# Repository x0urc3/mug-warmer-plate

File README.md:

# [Work-In-Progress] Mug Warmer Plate
A Mug Warmer PCB plate

## To Do
### Version 0.1-test
Create a PCB to test and evaluate hardware and firmware design
- ~~Circuit design~~
- ~~PCB design~~
- Manufacture PCB
- Firmware

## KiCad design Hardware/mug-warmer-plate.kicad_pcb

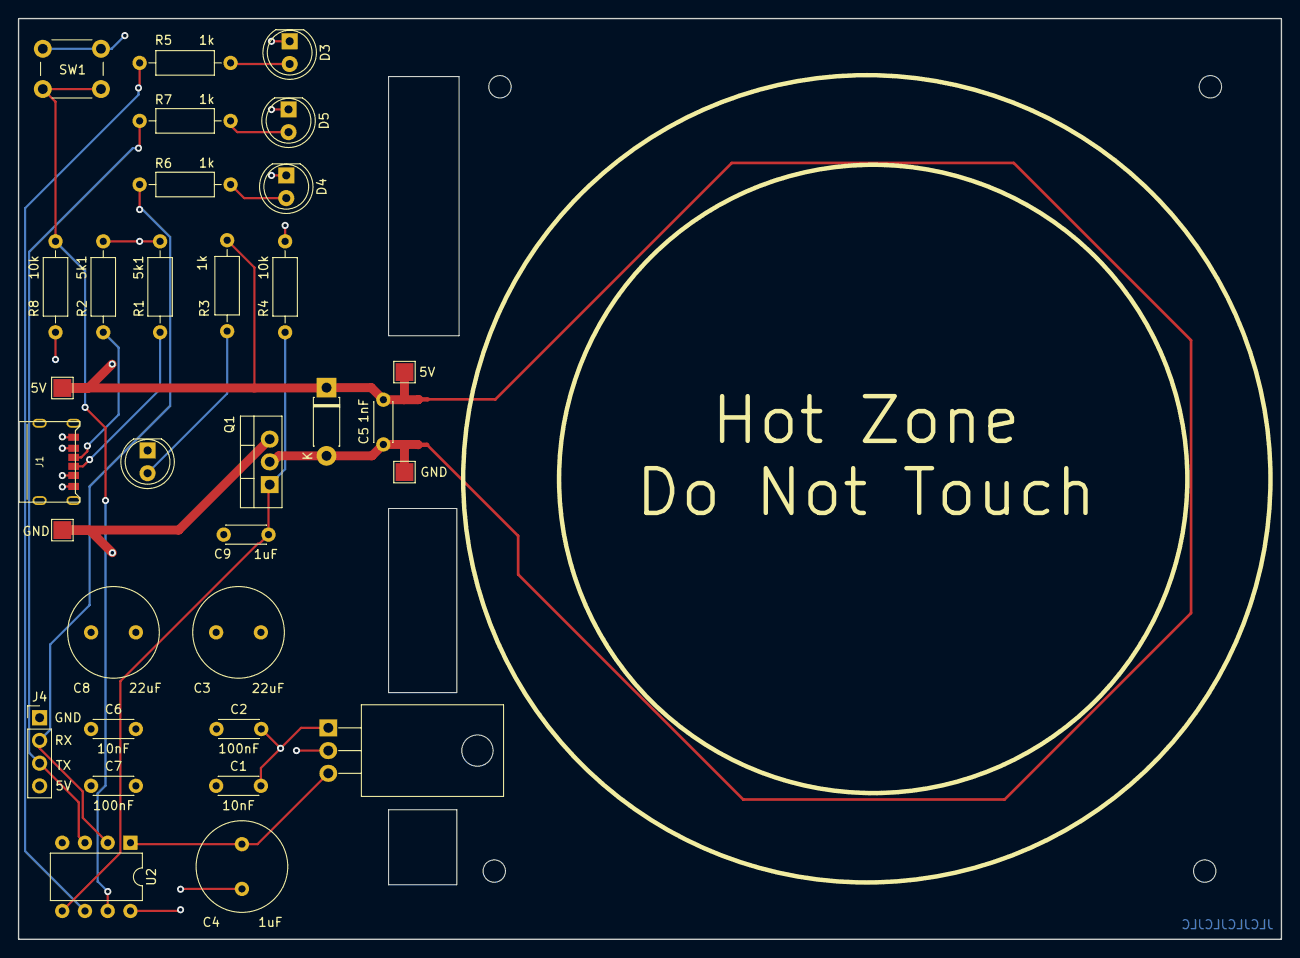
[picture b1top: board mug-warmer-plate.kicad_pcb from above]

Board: 4 copper layers, 141.1 x 102.9 mm, 34 parts (0 on the bottom side), 16 nets.

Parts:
C1, C6: 10nF; C_Disc_D4.3mm_W1.9mm_P5.00mm
C2, C7: 100nF; C_Disc_D4.3mm_W1.9mm_P5.00mm
C3, C8: 22uF; C_Radial_D10.0mm_H12.5mm_P5.00mm
C4: 1uF; C_Radial_D10.0mm_H12.5mm_P5.00mm
C5: 1nF; C_Disc_D4.3mm_W1.9mm_P5.00mm
C9: 1uF; C_Disc_D4.3mm_W1.9mm_P5.00mm
D1, D3, D4, D5: LED; LED_D5.0mm
D2: DIODE; D_DO-41_SOD81_P7.62mm_Horizontal
J1: USB_C_Receptacle_USB2.0; TYPE-C-31-M-17
J4: Conn_01x02_Male; PinHeader_1x04_P2.54mm_Vertical
NT1, NT2: NetTie_2; NetTie-2_SMD_Pad0.5mm
Q1: IRLZ44N; TO-220-3_Vertical
R1, R2: 5k1; R_Axial_DIN0207_L6.3mm_D2.5mm_P10.16mm_Horizontal
R3, R5, R6, R7: 1k; R_Axial_DIN0207_L6.3mm_D2.5mm_P10.16mm_Horizontal
R4, R8: 10k; R_Axial_DIN0207_L6.3mm_D2.5mm_P10.16mm_Horizontal
SW1: SW_DIP_x01; SW_PUSH_6mm_H4.3mm
TP1, TP3: 5V; TestPoint_Pad_2.0x2.0mm
TP2, TP4: GND; TestPoint_Pad_2.0x2.0mm
U1: LM35-NEB; TO-220-3_Horizontal_TabDown
U2: ATtiny85-20P; DIP-8_W7.62mm

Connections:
+5V: C1.2, C2.2, C3.2, C5.2, C6.2, C7.2, C8.2, D2.2 (A), J1.A4 (VBUS), J1.B9 (VBUS), J4.4, NT1.1, R3.1, SW1.2, TP1.1, TP3.1, U1.1 (+VS), U2.8 (VCC)
/RX: J4.3, R7.1, U2.3 (XTAL2/PB4)
/TX: J4.2, R6.1, U2.2 (XTAL1/PB3)
ELEMENT: NT1.2, NT2.2
GATE: C9.2, Q1.1 (G), R4.1, U2.5 (AREF/PB0)
GND: C1.1, C2.1, C3.1, C4.1, C6.1, C7.1, C8.1, C9.1, D1.1 (K), D3.1 (K), D4.1 (K), D5.1 (K), J1.A12 (GND), J1.B12 (GND), J4.1, Q1.3 (S), R1.2, R2.2, R4.2, R8.2, TP2.1, U1.2 (GND), U2.4 (GND)
unnamed: C5.1, D2.1 (K), NT2.1, Q1.2 (D), TP4.1
unnamed: D1.2 (A), R3.2
unnamed: D3.2 (A), R5.2
unnamed: D4.2 (A), R6.2
unnamed: D5.2 (A), R7.2
unnamed: J1.A5 (CC1), R2.1
unnamed: J1.B5 (CC2), R1.1
unnamed: R5.1, U2.6 (PB1)
unnamed: R8.1, SW1.1, U2.7 (PB2)
TEMP: C4.2, U1.3 (Vout), U2.1 (~RESET/PB5)

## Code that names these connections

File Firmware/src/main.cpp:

/* Copyright (c) 2022 Khairulmizam Samsudin <xource@gmail.com
 *
 * Firmware for mug warmer plate  
 */

/* Design Notes
 * - Switch pin should use AVR internal pullup
 * - Temperature sensor Vout connected to PB5/Reset
 * 	- ATTiny85 PB5/RESET would reset if input <0.3*Vcc i.e. 0.3*5=1.5V
 * 	- LM35 sensor 200-800mV for temperature between 20-80 celcius i.e. 10mV/Celcius 
 * 	- LM35 Vout connected to ground with 18KOhm can measure value between -55 to 150 celcius
 * 		- Resolution would be reduced
 */
#include <Arduino.h>
#include <SoftwareSerial.h>
//#include <TinySoftwareSerial.h> //Use Pin 5/0 and Pin 6/1 on ATTiny85/Arduino
//SoftwareSerial mySerial(4, 3); // RX, TX

#include <avr/io.h>
#include <util/delay.h>

// pinout                Phy  |   AVR |   Arduino
#define LEDPIN1     1  // 6       PB1         1
#define LEDPIN2     3  // 2       PB3         3
#define LEDPIN3     4  // 3       PB4         4
#define GATEPIN     0  // 5       PB0         0
#define TEMPPIN     A0 // 1       PB5         A0
#define SWITCHPIN   2  // 7       PB2         2

#define TEMP_GAIN	    1
#define TEMP_OFFSET	    410     // Biased at 2V. 2/5*1024=410
#define TEMP_SCALE      500     // LM35: 10mV per Celcius i.e. 5V/0.010 = 500
#define VRef            1.1                 
#define ITEMP_GAIN	    1
#define ITEMP_OFFSET    275     // Offet for 0deg Celcius	
#define ITEMP_SCALE     1       // AVR temp sensor: 1LSB per celcius    

static inline void initADC(void) {
    ADCSRA |= ((1 << ADPS1)| (1 << ADPS2)); // ADC clock prescaler /64. 8Mhz/64 = 125kHz
    ADCSRA |= (1 << ADEN);                  // enable ADC
}

uint16_t getTemp(void) { 
    uint16_t temp;
    ADMUX &= (~(1 << REFS1) | ~(1 << REFS0));   // Vcc as Voltage Ref 
    ADMUX &= 0xf0;                              // Select PB5 (ADC0)
    ADCSRA |= (1 << ADSC);                      // Start conversion
    loop_until_bit_is_clear(ADCSRA, ADSC);
    temp = TEMP_GAIN * (ADC - TEMP_OFFSET) * TEMP_SCALE / 1024; 
    return (temp); 
}

uint16_t getInternalTemp(void) { 
    uint16_t temp;
    ADMUX |= (1 << REFS1);   // Internal 1.1V Voltage Ref 
    ADMUX |= 0xff;           // Select ADC4
    ADCSRA |= (1 << ADSC);   // Start conversion
    loop_until_bit_is_clear(ADCSRA, ADSC);
    temp = ITEMP_GAIN * (ADC - ITEMP_OFFSET);
    return (temp);           
}

void setup() {
    pinMode(LEDPIN1, OUTPUT);
    pinMode(LEDPIN2, OUTPUT);
    pinMode(LEDPIN3, OUTPUT);
    pinMode(GATEPIN, OUTPUT);
    pinMode(TEMPPIN, INPUT);
    pinMode(SWITCHPIN, INPUT_PULLUP);

    //	Serial.begin(9600);
    //	mySerial.begin(9600);
    //    OSCCAL=200;
}

void loop() {


}

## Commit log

2022-05-11 Initial commit - Created .gitignore - Setup basic Kicad project file
2022-05-13 Added power supply block
2022-05-13 Updated ignore list
2022-05-13 Added microprocessor block
2022-05-13 Completed circuit schematic
2022-05-14 Replaced 5V pin with testpad
2022-05-14 Added USB-C-Power footprint from https://github.com/jenschr/USB-C-Connectors/tree/master/Kicad/Footprints/USB-C-Power-tester.pretty
2022-05-14 Defined all component footprint
2022-05-14 More fixes - Used 4 pin for serial communication i.e. 5v, RX, TX and GND - Remove GND and 5V net label to fix ERC warning
2022-05-14 Fix USB_C_Receptacle and ELEMENT net - Replace with USB_C_Receptacle_USB2.0 for smaller footprint in sheet - Added NetTie symbol and footprint to clearly differentiate ELEMENT net
2022-05-14 Initial PCB placement
2022-05-15 Complete routing and pass DRC check
2022-05-15 Added test point to test thermoelectric cooler
2022-05-15 Completed silkscreen layer
2022-05-15 Updated .gitignore
2022-05-15 Added cutout for thermal management
2022-05-15 Added JLPCB order number id
2022-05-18 Initialize firmware directory and define pins
2022-05-18 Update related to PlatformIO
2022-05-20 Added design notes and capitalized pins definition
2022-05-22 Add 2V bias to TEMP pin to prevent ATTiny85 from resetting
2022-05-22 Use ATTiny85 internal pullup resistor for switch
2022-05-23 Add functions for LM35 and AVR internal temperature sensor
2022-05-24 doc: Update WIP status
